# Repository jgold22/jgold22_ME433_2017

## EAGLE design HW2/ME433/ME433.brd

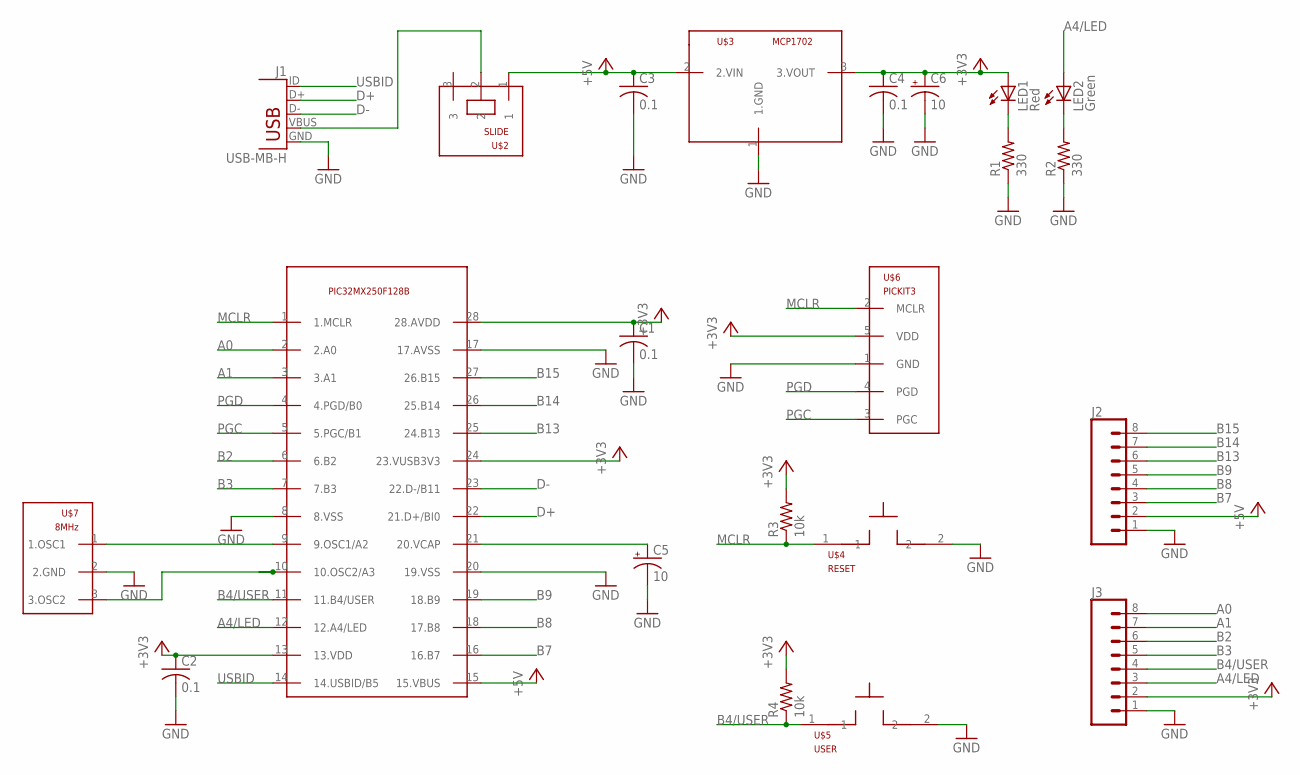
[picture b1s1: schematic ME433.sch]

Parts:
C1, C2, C3, C4: 0.1; C025-025X050
C5, C6: 10; B45181B
J1: USB-MB-H
J2, J3: CONN_08"; 1X08
LED1: Red; LED3MM
LED2: Green; LED3MM
R1, R2: 330; 0207/10
R3, R4: 10k; 0207/10
U$1: PIC32MX250F128B; DIL28-3
U$2: SLIDE
U$3: MCP1702; TO92
U$4: RESET; PB
U$5: USER; PB
U$6: PICKIT3; 1X05
U$7: 8MHz; OSC

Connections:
+3V3: C1.1, C2.1, C4.1, C6.+, J3.2, LED1.A, R3.2, R4.2, U$1.13 (13.VDD), U$1.24 (23.VUSB3V3), U$1.28 (28.AVDD), U$3.3 (3.VOUT), U$6.5 (VDD)
+5V: C3.1, J2.2, U$1.15 (15.VBUS), U$2.1, U$3.2 (2.VIN)
A0: J3.8, U$1.2 (2.A0)
A1: J3.7, U$1.3 (3.A1)
A4/LED: J3.3, LED2.A, U$1.12 (12.A4/LED)
B2: J3.6, U$1.6 (6.B2)
B3: J3.5, U$1.7 (7.B3)
B4/USER: J3.4, R4.1, U$1.11 (11.B4/USER), U$5.1
B7: J2.3, U$1.16 (16.B7)
B8: J2.4, U$1.18 (17.B8)
B9: J2.5, U$1.19 (18.B9)
B13: J2.6, U$1.25 (24.B13)
B14: J2.7, U$1.26 (25.B14)
B15: J2.8, U$1.27 (26.B15)
D+: J1.D+, U$1.22 (21.D+/BI0)
D-: J1.D-, U$1.23 (22.D-/B11)
GND: C1.2, C2.2, C3.2, C4.2, C5.-, C6.-, J1.GND, J2.1, J3.1, R1.1, R2.1, U$1.8 (8.VSS), U$1.17 (17.AVSS), U$1.20 (19.VSS), U$3.1 (1.GND), U$4.2, U$5.2, U$6.1 (GND), U$7.2 (2.GND)
MCLR: R3.1, U$1.1 (1.MCLR), U$4.1, U$6.2 (MCLR)
unnamed: J1.VBUS, U$2.2
unnamed: LED2.K (C), R2.2
unnamed: LED1.K (C), R1.2
unnamed: U$1.9 (9.OSC1/A2), U$7.1 (1.OSC1)
unnamed: U$1.10 (10.OSC2/A3), U$7.3 (3.OSC2)
unnamed: C5.+, U$1.21 (20.VCAP)
PGC: U$1.5 (5.PGC/B1), U$6.3 (PGC)
PGD: U$1.4 (4.PGD/B0), U$6.4 (PGD)
USBID: J1.ID, U$1.14 (14.USBID/B5)

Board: 2 copper layers, 22 parts (0 on the bottom side), 27 nets, no tracks yet.

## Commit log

2017-03-30 HW1code
    Device Configurations set
2017-03-30 Circuit Diagram
2017-03-30 Breadboard
2017-03-30 toggle LED
2017-04-04 Eagle Library
2017-04-04 eagle schematic
2017-04-07 Voltage Regulator Circuit
2017-04-07 Homework 3 board design
2017-04-11 Added LED and user button
2017-04-12 Added Libraries
2017-04-13 Edited Code
2017-04-15 Finish code
2017-04-17 Created Libraries
2017-04-17 Added main function
2017-04-20 LCD code
2017-04-20 Edit I2C code
2017-04-21 initialize IMU
2017-04-25 IMU code
2017-04-26 progress bar timing
2017-05-03 hmwk
2017-05-03 hwk8
2017-05-10 Hello world app
2017-05-13 finish imu
2017-05-26 Camera App
2017-05-29 Android USB app
2017-05-31 harmony file
2017-06-04 initialized pic code
2017-06-04 finish pic code
2017-06-04 finish motor control code
2017-06-07 Image Processing
2017-06-07 Android MC
2017-06-08 motor control
2017-06-08 final pic
2017-06-08 final motor control
